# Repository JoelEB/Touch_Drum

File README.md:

# Touch_Drum
A repo for all thing TouchDrum Related: hardware/software files, 3D files, etc.

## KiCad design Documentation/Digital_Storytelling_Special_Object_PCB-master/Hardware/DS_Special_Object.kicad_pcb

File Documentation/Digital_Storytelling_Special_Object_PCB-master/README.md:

# Digital_Storytelling_Special_Object_PCB
A custom PCB to fit inside of special objects for DS vertical slice.

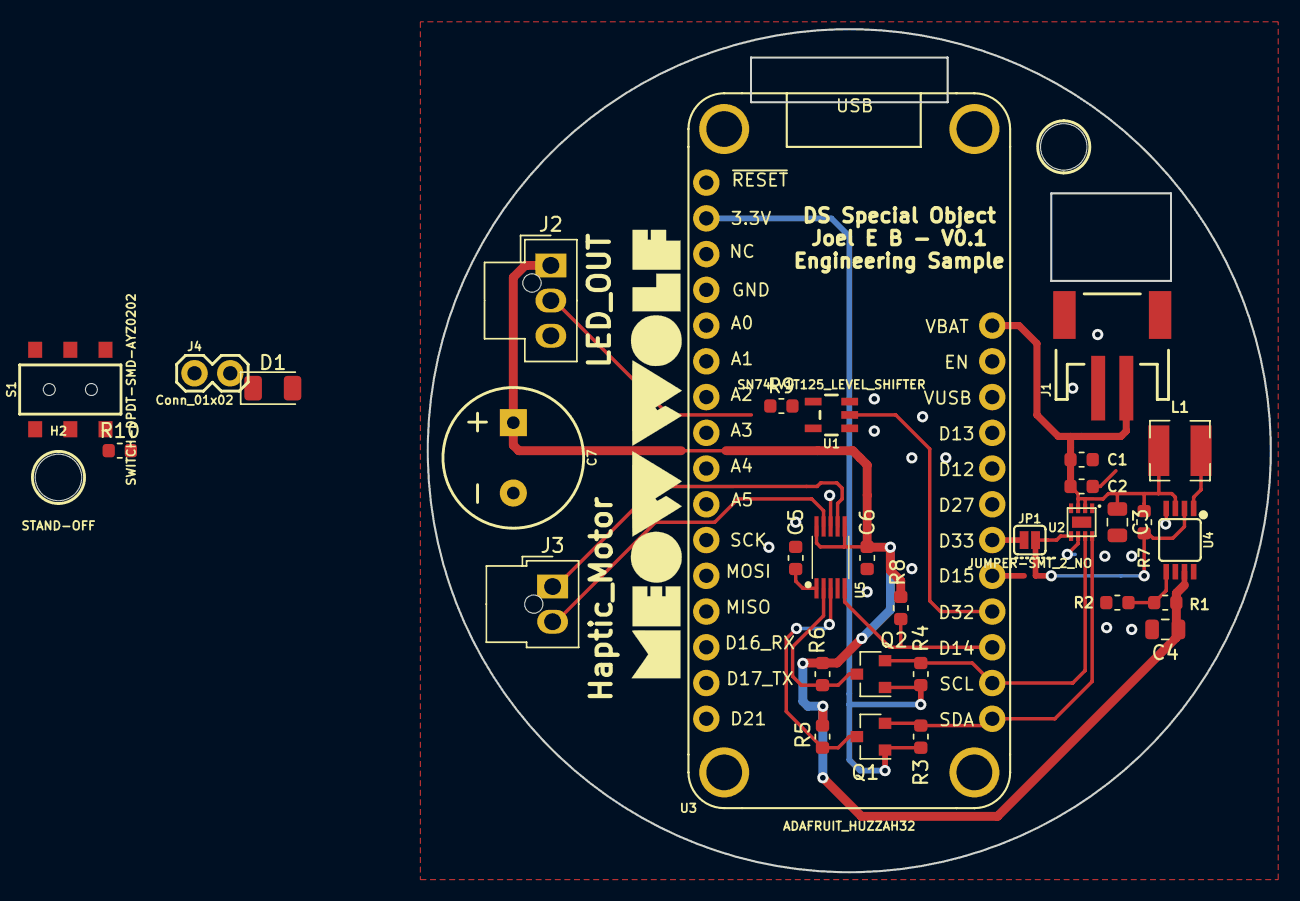
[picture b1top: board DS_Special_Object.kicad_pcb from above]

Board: 2 copper layers, 59.9 x 59.9 mm, 36 parts (0 on the bottom side), 22 nets.

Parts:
BT1: LIPO-OUTLINE2000; LIPO-1000
C1, C6: 0.1uF; C_0603_1608Metric
C2: 10uF; C_0603_1608Metric
C3, C4: 22uF; R_0805_2012Metric
C5: 1.0uF; C_0603_1608Metric
C7: 1000UF; CPOL-RADIAL-5MM-10MM
D1: LED; LED_1206_3216Metric
H1, H2: STAND-OFF
J1: JST_2MM_MALE; JST-2-SMD
J2: Conn_01x03; Molex_Nano-Fit_105309-xx03_1x03_P2.50mm_Vertical
J3: Conn_01x02; Molex_Nano-Fit_105309-xx02_1x02_P2.50mm_Vertical
J4: Conn_01x02; 1X02
JP1: JUMPER-SMT_2_NO; SMT-JUMPER_2_NO_SILK
L1: 2.2UH; L_Bourns-SRN4026
LOGO1: MeowWolf_Logo_Horizontal; MW_Logo_Horizontal_1.25inch
Q1, Q2: BSS138; SOT-23
R1: 750KΩ; R_0603_1608Metric
R2: 100KΩ; R_0603_1608Metric
R3, R4, R5, R6, R7, R8: 10KΩ; R_0603_1608Metric
R9, R10: 330Ω; R_0603_1608Metric
S1: SWITCH-DPDT-SMD-AYZ0202; SWITCH_DPDT_SMD_AYZ0202
U1: SN74LV1T125_LEVEL_SHIFTER; SOT23-5
U2: MAX17048DFN8; DFN-8
U3: ADAFRUIT_HUZZAH32
U4: PAM2401; MSOP8
U5: DRV2605L; VSSOP-10

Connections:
+3V3: Q1.1, Q2.1, R3.1, R4.1, R10.1, U3.2
+5V: C4.1, C6.1, C7.+, J2.1, R1.1, R5.2, R6.2, R8.1, U1.5, U4.7, U5.P$6, U5.P$10
ALERT: U2.P$5, U3.22
EN: R7.2, U3.21, U4.2
GND: C1.2, C2.2, C3.2, C4.2, C5.2, C6.2, C7.-, D1.1, J1.1, J2.3, J4.1, R2.2, U1.1, U1.3, U2.P$1, U2.P$4, U2.P$6, U2.P$9, U3.4, U4.4, U4.8, U5.P$8
LED: U1.2, U3.20
LED_BUFFERED: R9.2, U1.4
LIPO: C1.1, C2.1, C3.1, JP1.2, L1.1, R7.1, S1.1, S1.4, U2.P$2, U2.P$3, U3.28, U4.3
MOTOR_EN: R8.2, U3.19, U5.P$5
unnamed: C5.1, U5.P$1
unnamed: D1.2, R10.2
unnamed: J1.2, JP1.1, S1.2, S1.5
unnamed: J2.2, R9.1
unnamed: L1.2, U4.1
unnamed: R1.2, R2.1, U4.5
OUT+: J3.1, U5.P$7
OUT-: J3.2, U5.P$9
SCL_3V3: Q2.2, R4.2, U2.P$7, U3.18
SCL_5V: Q2.3, R6.1, U5.P$2
SDA_3V3: Q1.2, R3.2, U2.P$8, U3.17
SDA_5V: Q1.3, R5.1, U5.P$3
VUSB: J4.2, U3.26

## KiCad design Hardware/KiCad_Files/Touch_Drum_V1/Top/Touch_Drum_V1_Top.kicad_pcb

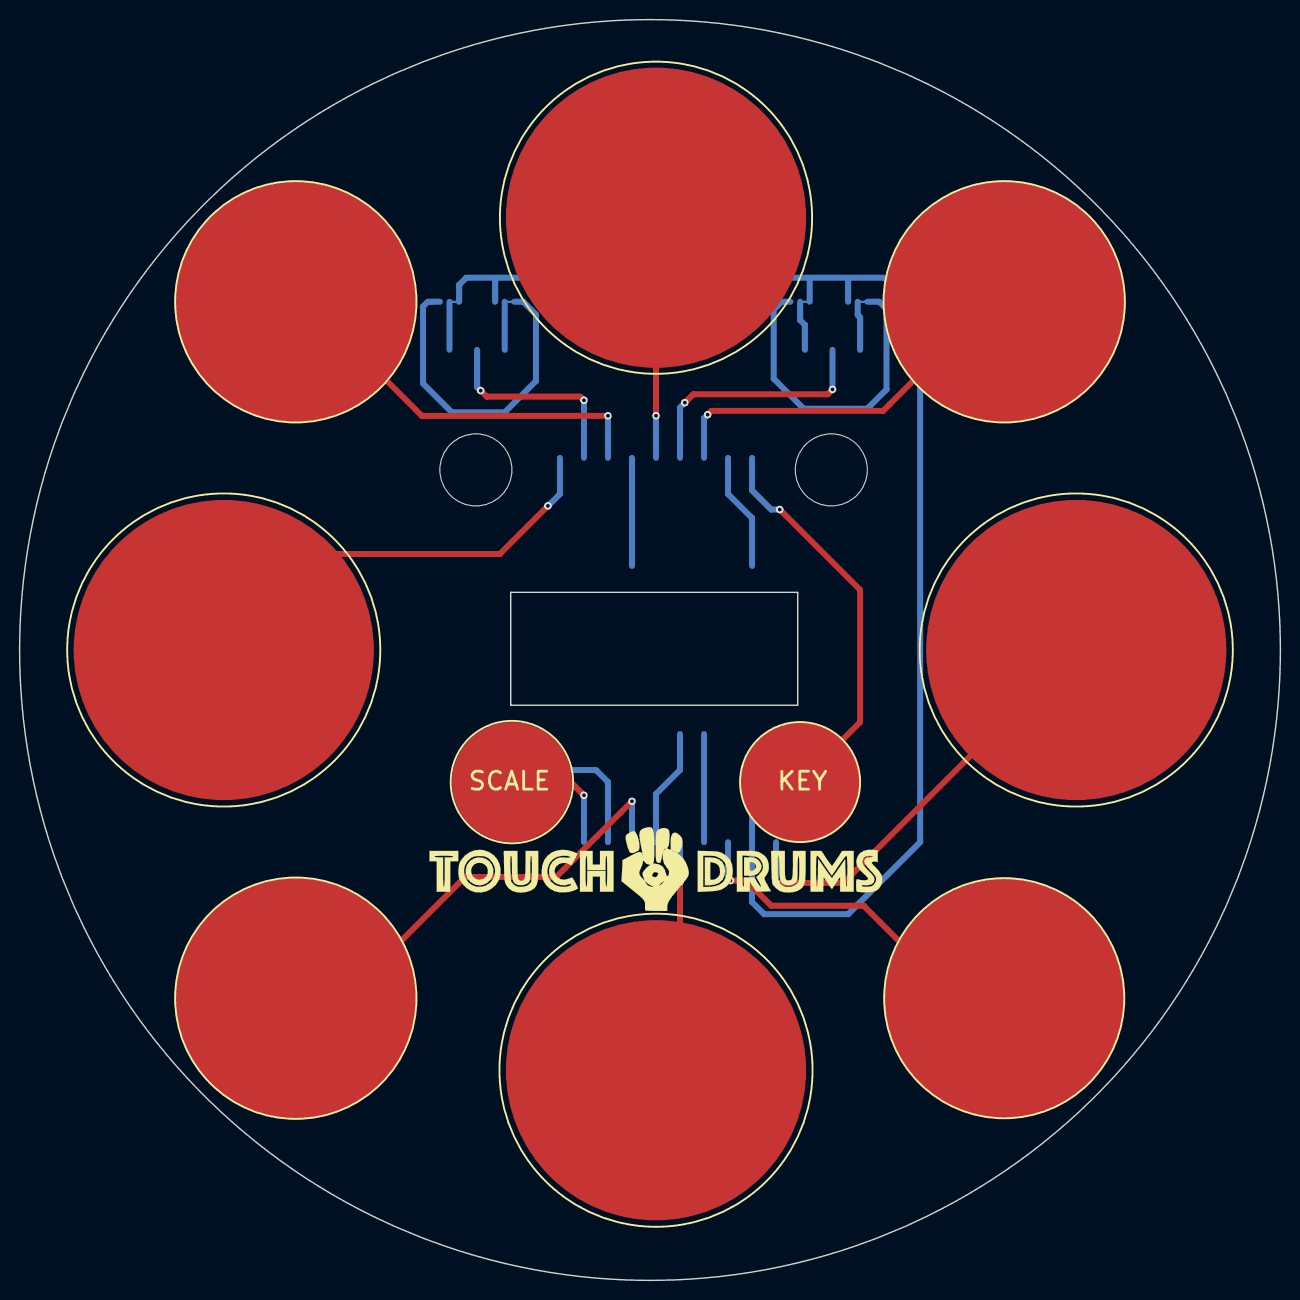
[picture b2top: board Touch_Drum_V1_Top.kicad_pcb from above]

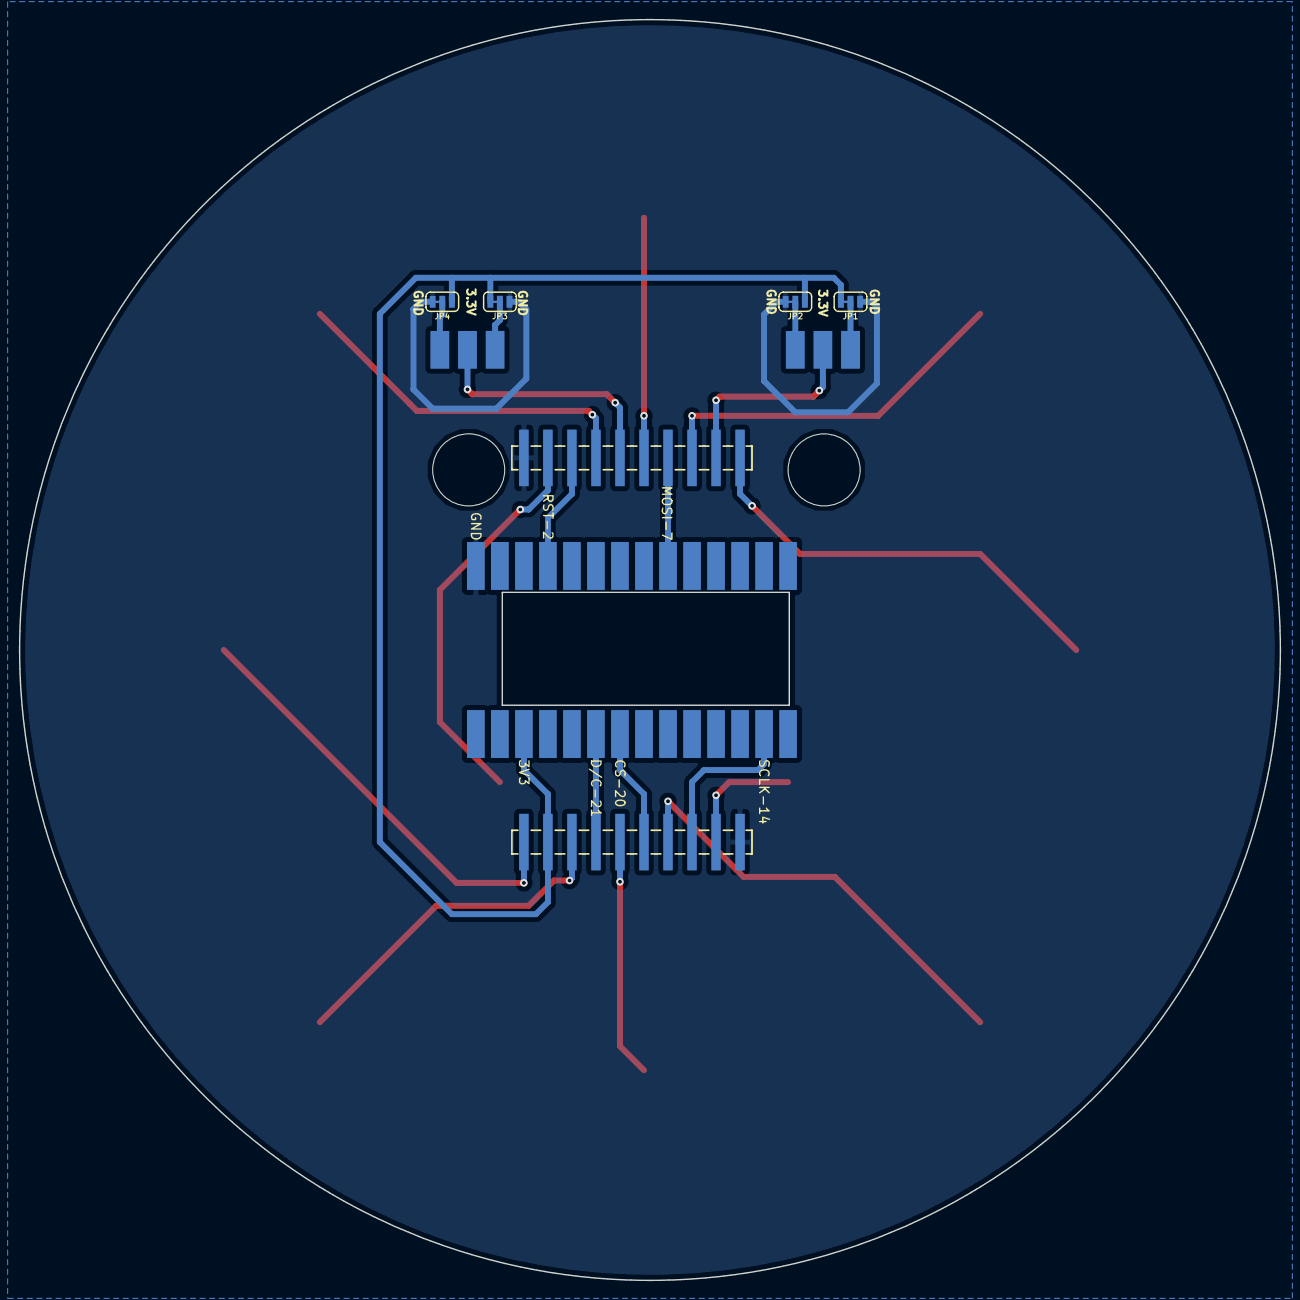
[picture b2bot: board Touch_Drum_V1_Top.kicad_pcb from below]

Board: 2 copper layers, 133.4 x 133.4 mm, 20 parts (8 on the bottom side), 23 nets.

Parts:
J1, J2: Conn_01x10; 1X10_SMD_MALE
JP1, JP2, JP3, JP4: JP_3_1-NC; SMT-JUMPER_3_1-NC_TRACE_SILK
L1: LOGO; TouchDrumLogo
TP1: PAD_0; PAD.LARGE_0.5INCH
TP2: PAD_1; PAD.LARGE_1.0INCH
TP3: PAD_2; PAD.LARGE_1.25INCH
TP4: PAD_3; PAD.LARGE_1.0INCH
TP5: PAD_4; PAD.LARGE_1.25INCH
TP6: PAD_5; PAD.LARGE_1.25INCH
TP7: PAD_6; PAD.LARGE_1.0INCH
TP8: PAD_7; PAD.LARGE_1.25INCH
TP9: PAD_8; PAD.LARGE_1.0INCH
TP10: PAD_9; PAD.LARGE_0.5INCH
U1: TeensyView
VR1, VR2: TRIMPOT; Panel_Mount_Potentiometer

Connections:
+3V3: J1.2, JP1.3, JP2.1, JP3.3, JP4.1, U1.12
CS: J1.6, U1.8
DC: J1.4, U1.9
DECAY_KNOB: J2.6, VR2.2
GND: J1.10, J2.10, JP1.1, JP2.3, JP3.1, JP4.3, U1.15
MOSI: J2.4, U1.23
unnamed: JP1.2, VR1.1
unnamed: JP2.2, VR1.3
unnamed: JP3.2, VR2.1
unnamed: JP4.2, VR2.3
RST: J2.8, U1.18
SCLK: J1.8, U1.2
TOUCH_0: J1.9, TP1.1
TOUCH_1: J1.7, TP2.1
TOUCH_2: J1.5, TP3.1
TOUCH_3: J1.3, TP4.1
TOUCH_4: J1.1, TP5.1
TOUCH_5: J2.5, TP6.1
TOUCH_6: J2.3, TP7.1
TOUCH_7: J2.1, TP8.1
TOUCH_8: J2.7, TP9.1
TOUCH_9: J2.9, TP10.1
VOL_KNOB: J2.2, VR1.2

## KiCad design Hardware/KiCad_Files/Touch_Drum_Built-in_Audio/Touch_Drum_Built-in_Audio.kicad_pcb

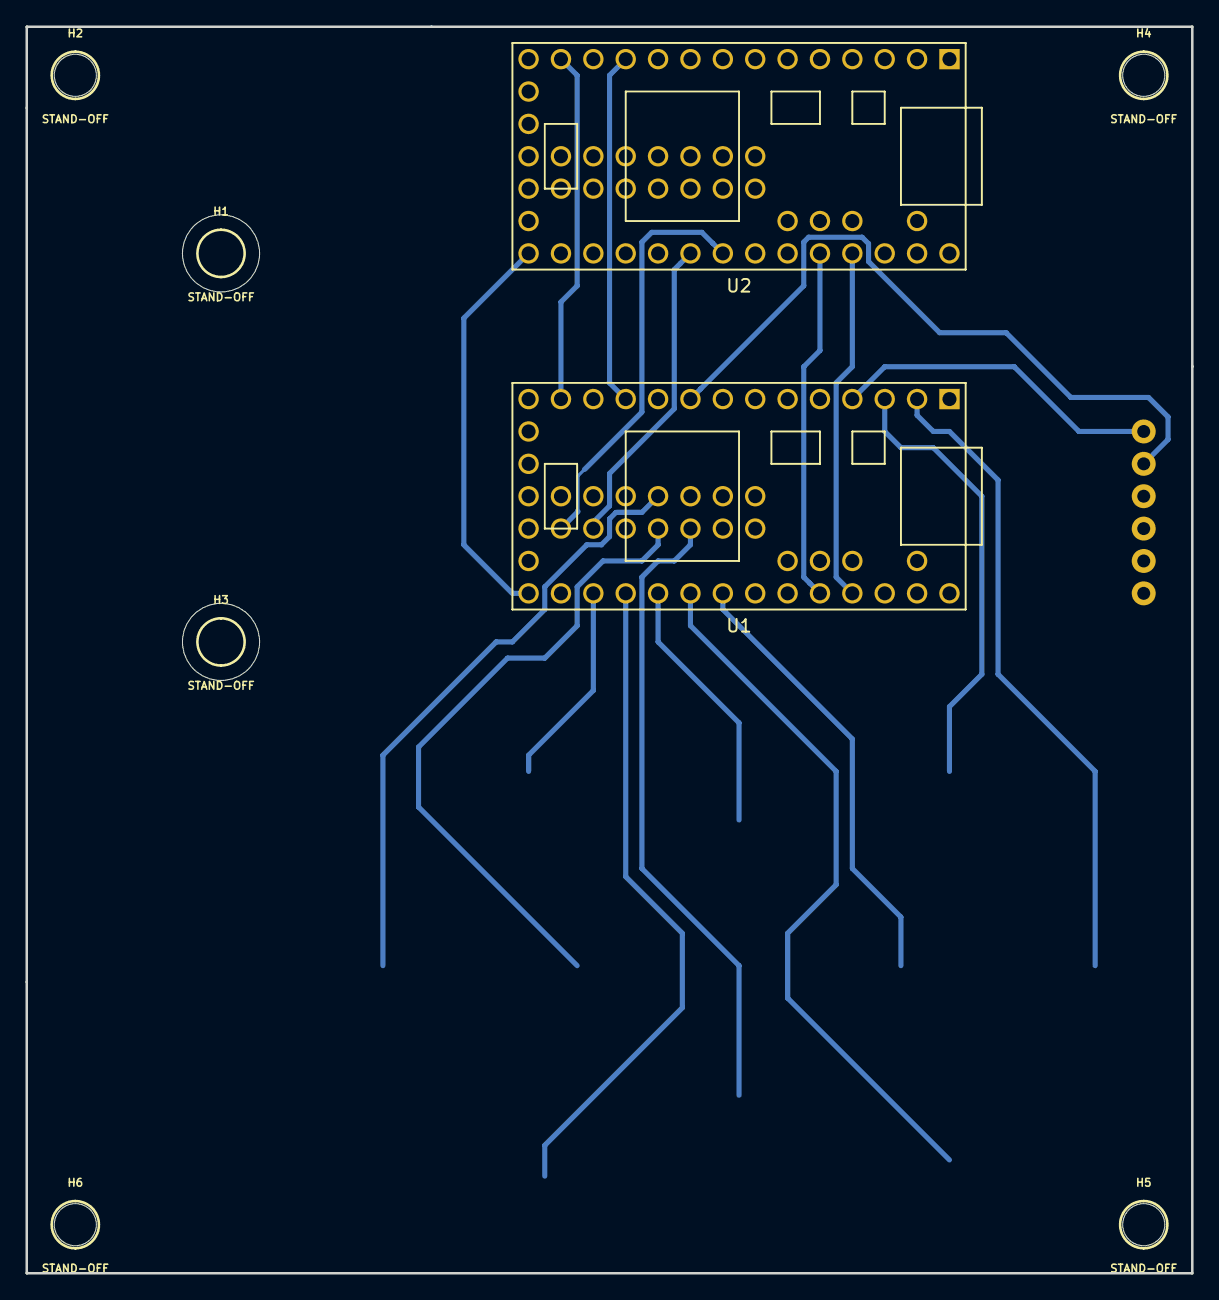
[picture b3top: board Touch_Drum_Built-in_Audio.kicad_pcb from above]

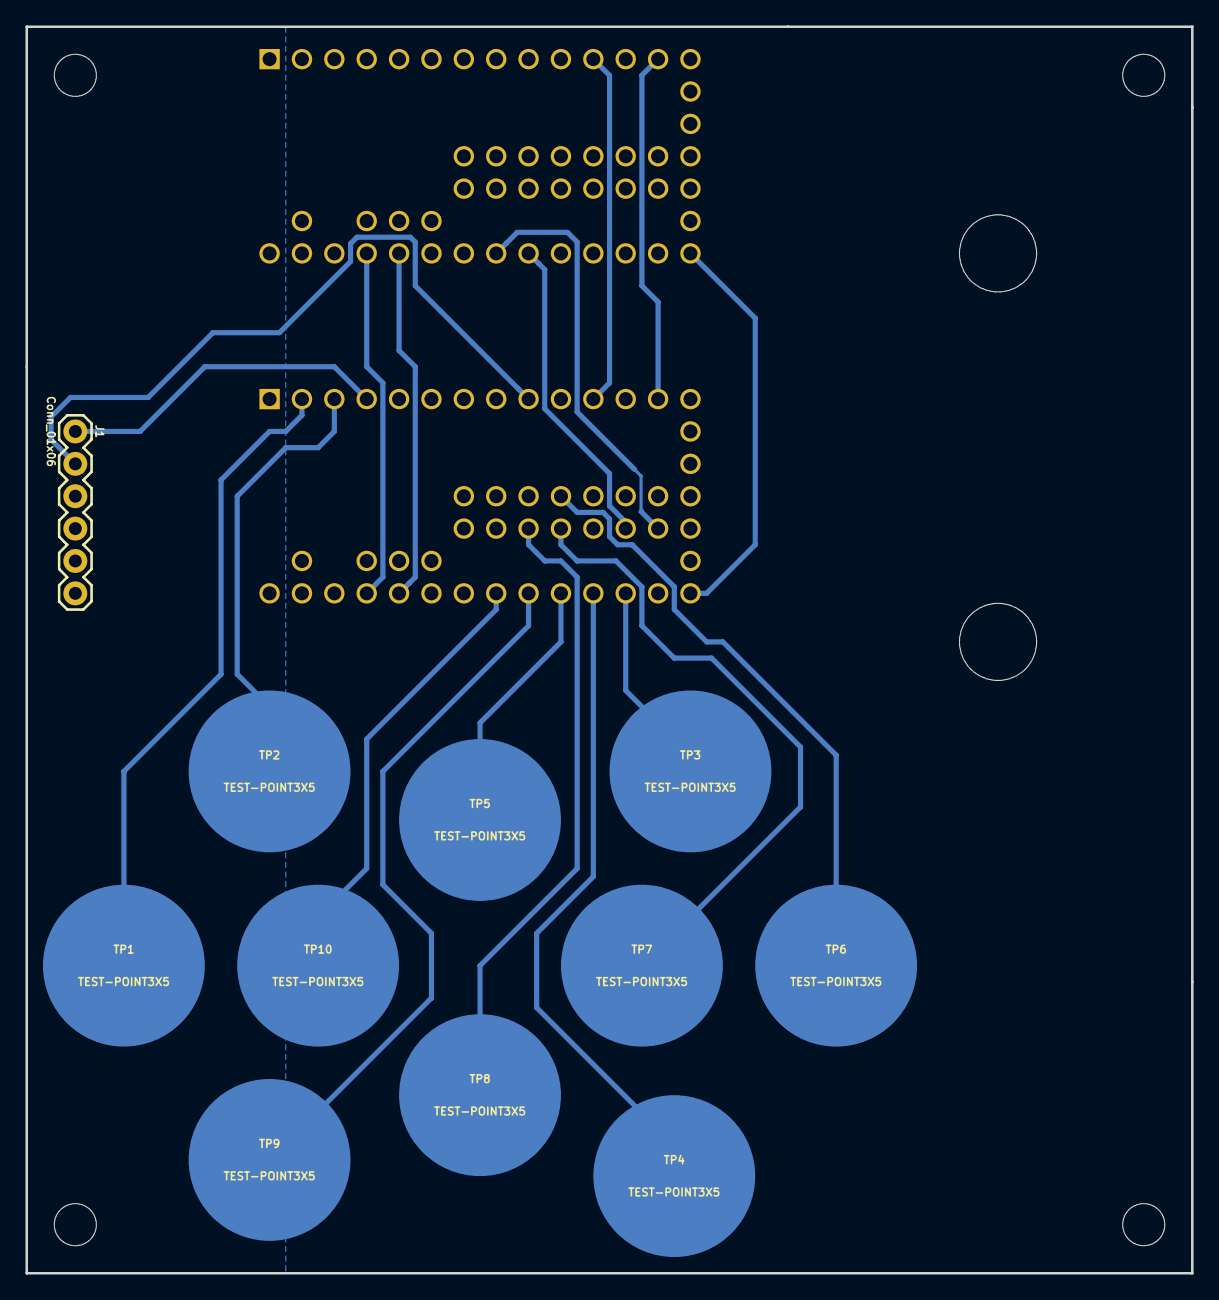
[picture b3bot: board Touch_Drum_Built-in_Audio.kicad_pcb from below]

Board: 2 copper layers, 91.4 x 97.8 mm, 19 parts (11 on the bottom side), 23 nets.

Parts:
H1, H2, H3, H4, H5, H6: STAND-OFF
J1: Conn_01x06; 1X06
TP1, TP2, TP3, TP4, TP5, TP6, TP7, TP8, TP9, TP10: TEST-POINT3X5; PAD.LARGE
U1: TEENSY_3.2_FULL_PINS; TEENSY_3.1-3.2_FULL_PINS
U2: Audio_Shield; TEENSY_3.1-3.2_FULL_PINS

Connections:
AUDIO_BCLK: U1.11, U2.11
AUDIO_DIN: U1.29, U2.29
AUDIO_DOUT: U1.20, U2.20
AUDIO_LRCLK: U1.30, U2.30
AUDIO_MCLK: U1.13, U2.13
GND: J1.6, U1.1, U2.1
OLED_CS: J1.4, U1.27
OLED_DC: J1.5, U1.28
OLED_MOSI: J1.2, U1.9
OLED_RST: J1.1, U1.4
OLED_SCK: J1.3, U1.21
SCL1: U1.45, U2.26
SDA1: U1.46, U2.25
TOUCH_0: TP1.P$1, U1.2
TOUCH_1: TP2.P$1, U1.3
TOUCH_2: TP3.P$1, U1.22
TOUCH_3: TP4.P$1, U1.23
TOUCH_4: TP5.P$1, U1.24
TOUCH_5: TP6.P$1, U1.41
TOUCH_6: TP7.P$1, U1.48
TOUCH_7: TP8.P$1, U1.49
TOUCH_8: TP9.P$1, U1.25
TOUCH_9: TP10.P$1, U1.26

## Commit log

2018-09-21 Adding website files
2018-09-21 Adding Millable PCB
2018-09-21 Updating Millable Version
2018-09-21 Update gitignore to include DRL files for gerbers
2018-09-21 Adding DRL
2018-09-24 Adding code for milled prototype
2018-09-25 Beginning Full Layout
2018-10-02 Adding functional code with Toudh Drum splash screen for all versions
2018-10-06 Adding V5 firmware
    V5 includes: MIDI, MIDI scales, overhaul of the touchRead function into one 'for loop(), adding debounce for capTouchRead buttons. Also adding lots of support files from Marshall's repository.
2018-10-06 Starting cleanup, adding master file for tupperware proto
2018-10-12 Adding Master firmware for each model
2018-10-13 Integrating multple wavefrom code with both masters
2018-10-14 Adding nRF52 BLE to Serial code
    Adding nRF52 BLE to Serial code. This was testing with the Oval app connected to the nRF52 over BLE and the nRF52 connected to a serial terminal on mac with an FTDI basic.
2018-10-25 Adding 3D and BLE files
2018-11-14 Adding a few more 3D files
2018-12-07 Mostly complete Top layer PCB of V1 Touch Drum
2018-12-20 Adding more logos
2019-08-13 Adding more reference files
